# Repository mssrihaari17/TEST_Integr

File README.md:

View this project on [CADLAB.io](https://cadlab.io/project/29905). 

# TEST_Integr

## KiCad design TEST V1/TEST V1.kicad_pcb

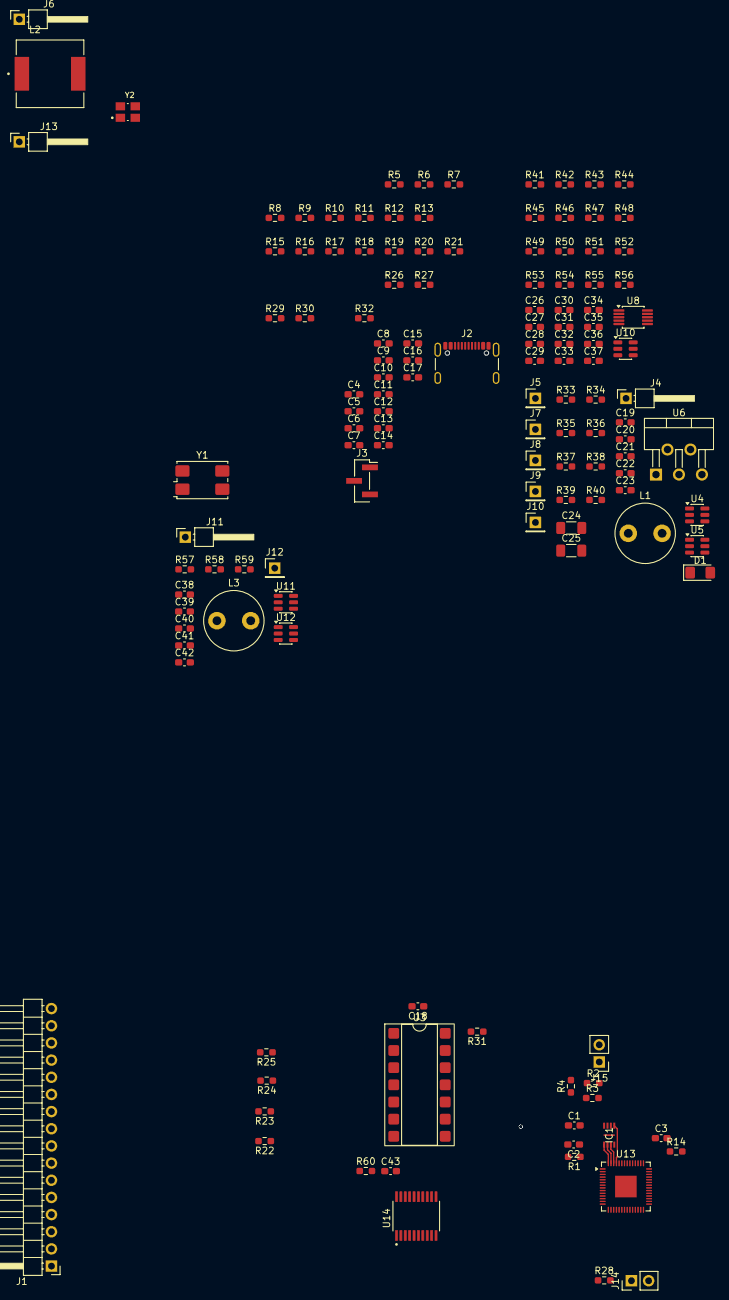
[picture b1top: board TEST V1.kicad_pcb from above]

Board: 2 copper layers, 135 parts (0 on the bottom side), 107 nets.

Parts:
C1, C3, C6, C15: 2u2; C_0603_1608Metric_Pad1.08x0.95mm_HandSolder
C2, C4, C5, C7, C8, C9, C10, C11, C12, C13, C14, C18, C20, C31, C32, C33, C37, C39, C43: 100n; C_0603_1608Metric_Pad1.08x0.95mm_HandSolder
C16, C17: 27p; C_0603_1608Metric_Pad1.08x0.95mm_HandSolder
C19, C26, C27, C30, C34, C35, C36, C38: 10u; C_0603_1608Metric_Pad1.08x0.95mm_HandSolder
C21, C40: 0.1u; C_0603_1608Metric_Pad1.08x0.95mm_HandSolder
C22, C23, C41, C42: 22u; C_0603_1608Metric_Pad1.08x0.95mm_HandSolder
C24, C25: C_Polarized; C_1206_3216Metric_Pad1.33x1.80mm_HandSolder
C28: 10n; C_0603_1608Metric_Pad1.08x0.95mm_HandSolder
C29: 1u; C_0603_1608Metric_Pad1.08x0.95mm_HandSolder
D1: 1N5820; D_1206_3216Metric_Pad1.42x1.75mm_HandSolder
IC1: W25Q16JVUXIQ; SON50P300X200X60-9N
J1: Conn_01x16_Socket; PinHeader_1x16_P2.54mm_Horizontal
J2: USB_C_Receptacle_USB2.0_14P; USB_C_Receptacle_GCT_USB4105-xx-A_16P_TopMnt_Horizontal
J3: Conn_01x03_Socket; PinHeader_1x03_P2.00mm_Vertical_SMD_Pin1Right
J4, J6, J11, J13: Conn_01x02_Pin; PinHeader_1x01_P2.54mm_Horizontal
J5, J12: PinHeader_1x01_P2.54mm_Vertical
J7, J8, J9, J10: Conn_01x01_Pin; PinHeader_1x01_P2.54mm_Vertical
J14, J15: Conn_01x02_Pin; PinHeader_1x02_P2.54mm_Vertical
L1, L3: 16u; L_Radial_D8.7mm_P5.00mm_Fastron_07HCP
L2: 33u; IND_1274AS-H-150M=P3
R1, R3, R14, R18, R19, R20, R31, R60: 0; R_0603_1608Metric_Pad0.98x0.95mm_HandSolder
R2, R32, R48, R49: 1k; R_0603_1608Metric_Pad0.98x0.95mm_HandSolder
R4, R28, R35, R50, R51, R53, R55, R59: 10k; R_0603_1608Metric_Pad0.98x0.95mm_HandSolder
R5, R6: 27R; R_0603_1608Metric_Pad0.98x0.95mm_HandSolder
R7, R8, R9, R10, R11, R12, R13, R15, R36, R37, R38, R39, R40, R41, R44, R45, R46, R47, R52, R54, R56: 0R; R_0603_1608Metric_Pad0.98x0.95mm_HandSolder
R16, R17: 1k5; R_0603_1608Metric_Pad0.98x0.95mm_HandSolder
R21: 200R; R_0603_1608Metric_Pad0.98x0.95mm_HandSolder
R22, R23, R24, R25: 100R; R_0603_1608Metric_Pad0.98x0.95mm_HandSolder
R26, R27: 5K1; R_0603_1608Metric_Pad0.98x0.95mm_HandSolder
R29: 5K6; R_0603_1608Metric_Pad0.98x0.95mm_HandSolder
R30: 10K; R_0603_1608Metric_Pad0.98x0.95mm_HandSolder
R33, R57: 100k; R_0603_1608Metric_Pad0.98x0.95mm_HandSolder
R34, R58: 190k; R_0603_1608Metric_Pad0.98x0.95mm_HandSolder
R42, R43: 2.4k; R_0603_1608Metric_Pad0.98x0.95mm_HandSolder
U3: 74AHCT125; DIP-14_W7.62mm_SMDSocket_SmallPads
U4, U11: TPS54202DDC; SOT-23-6
U5, U10, U12: MCP4725A2T-ECH; SOT-23-6
U6: LM2596T-5; TO-220-5_P3.4x3.7mm_StaggerOdd_Lead3.8mm_Vertical
U8: AD9833; MSOP-10_3x3mm_P0.5mm
U13: RP2040; QFN-56-1EP_7x7mm_P0.4mm_EP3.2x3.2mm
U14: SN74LVC244APWT; SOP65P640X120-20N
Y1: Crystal_12MHz; Crystal_SMD_7050-4Pin_7.0x5.0mm
Y2: 25 MHz; XTAL_C3E-16.000-12-1015-X-M

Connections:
3v3: J1.15, R1.1, R3.1, R15.2, R16.1, R17.1, R18.1, R19.1, R20.1, R28.1, R45.2, R46.2, R60.1, U5.3 (VDD), U5.6 (A0), U12.3 (VDD), U12.6 (A0)
5V: R31.1, R47.2, R56.2
12V: R44.1, R54.1
+1V1: C3.1, R14.1, U13.45 (VREG_VOUT)
-12V: R41.1, R52.1
/DVDD: C4.1, C5.1, R14.2, U13.23 (DVDD), U13.50 (DVDD)
/Fn Gen/FG_OUT: R42.1, U8.10 (VOUT)
/Fn Gen/OFFSET: R50.1, U10.1 (VOUT)
/GPIO8: U3.2, U13.11 (GPIO8)
/GPIO9: U3.5, U13.12 (GPIO9)
/GPIO10: U3.9, U13.13 (GPIO10)
/GPIO11: U3.12, U13.14 (GPIO11)
/GPIO24: R29.2, R30.1, U13.36 (GPIO24)
/IOVDD: R7.1, R8.1, R9.1, R10.1, R11.1, R12.1, R13.1
/LA0_IN: J1.1, U14.2 (1A1)
/LA1_IN: J1.2, U14.4 (1A2)
/LA2_IN: J1.3, U14.6 (1A3)
/LA3_IN: J1.4, U14.8 (1A4)
/LA4_IN: J1.5, U14.11 (2A1)
/LA5_IN: J1.6, U14.13 (2A2)
/LA6_IN: J1.7, U14.15 (2A3)
/LA7_IN: J1.8, U14.17 (2A4)
/PG0_OUT: J1.9, R22.2
/PG1_OUT: J1.10, R23.2
/PG2_OUT: J1.11, R24.2
/PG3_OUT: J1.12, R25.2
/POWER SUPPLY/EN: J5.1, R33.1, U4.5 (EN)
/POWER SUPPLY/RPS_VOUT: C22.1, C23.1, J6.1, L1.2, R34.1
/POWER SUPPLY/TPS_FB: R34.2, R35.1, U4.4 (FB), U5.1 (VOUT)
/POWER SUPPLY/VIN: C24.1, R36.2, R37.1
/POWER SUPPLY/VOUT: C25.1, L2.2, R39.2, R40.1
/QSPI_CSN: IC1.1 (~CS), R2.1, R4.2, U13.56 (QSPI_SS)
/QSPI_SCLK: IC1.6 (CLK), U13.52 (QSPI_SCLK)
/QSPI_SD0: IC1.5 (DI_(IO0)), U13.53 (QSPI_SD0)
/QSPI_SD1: IC1.2 (DO_(IO1)), U13.55 (QSPI_SD1)
/QSPI_SD2: IC1.3 (~WP_(IO2)), U13.54 (QSPI_SD2)
/QSPI_SD3: IC1.7 (~HOLD_OR_RESET_(IO3)), U13.51 (QSPI_SD3)
/RPS/EN: J12.1, R57.1, U11.5 (EN)
/RPS/RPS_VOUT: C41.1, C42.1, J13.1, L3.2, R58.1
/RPS/TPS_FB: R58.2, R59.1, U11.4 (FB), U12.1 (VOUT)
/RUN: J14.1, R28.2, U13.26 (RUN)
/SWCLK: J3.1, U13.24 (SWCLK)
/SWD: J3.2, U13.25 (SWD)
/USB_DM: J2.A7 (D-), J2.B7 (D-), R6.2
/USB_DP: J2.A6 (D+), J2.B6 (D+), R5.2
/VBUS: J2.A4 (VBUS), J2.A9 (VBUS), J2.B4 (VBUS), J2.B9 (VBUS), R29.1
/XIN: C16.1, U13.20 (XIN), Y1.1
/XOUT: R32.1, U13.21 (XOUT)
ADC_AVDD: C14.1, C15.1, R21.1, U13.43 (ADC_AVDD)
GND: C1.1, C2.2, C3.2, C4.2, C5.2, C6.2, C7.2, C8.2, C9.2, C10.2, C11.2, C12.2, C13.2, C14.2, C15.2, C16.2, C17.2, C18.2, C19.2, C20.2, C22.2, C23.2, C24.2, C25.2, C26.1, C27.2, C29.1, C30.1, C31.1, C32.1, C33.2, C34.1, C35.2, C36.1, C37.1, C38.2, C39.2, C41.2, C42.2, C43.2, D1.2 (A), IC1.4 (GND), J1.16, J2.A1 (GND), J2.A12 (GND), J2.B1 (GND), J2.B12 (GND), J2.S1 (SHIELD), J3.3, J8.1, J10.1, J14.2, J15.2, R26.2, R27.2, R30.2, R33.2, R35.2, R43.1, R49.2, R57.2, R59.2, U3.1, U3.4, U3.7 (GND), U3.10, U3.13, U4.1 (GND), U5.2 (VSS), U6.3 (GND), U6.5 (~ON/OFF), U8.4 (DGND), U8.9 (AGND), U10.2 (VSS), U10.6 (A0), U11.1 (GND), U12.2 (VSS), U13.19 (TESTEN), U13.57 (GND), U14.1 (~1OE), U14.10 (GND), U14.19 (~2OE), Y1.2, Y1.4, Y2.2 (GND), Y2.4 (GND)
I2C_SCL: R17.2, U10.5 (SCL), U12.5 (SCL), U13.16 (GPIO13)
I2C_SDA: R16.2, U10.4 (SDA), U12.4 (SDA), U13.15 (GPIO12)
unnamed: C17.1, R32.2, Y1.3
unnamed: C30.2, C32.2, R47.1, R48.1
unnamed: C31.2, R46.1, Y2.1
unnamed: D1.1 (K), L2.1, R38.2
unnamed: C1.2, C2.1, IC1.8 (VCC), R1.2
unnamed: J2.A5 (CC1), R26.1
unnamed: J2.B5 (CC2), R27.1
unnamed: C19.1, C20.1, J4.1, U4.3 (VIN)
unnamed: J7.1, R36.1
unnamed: J9.1, R40.2
unnamed: C38.1, C39.1, J11.1, U11.3 (VIN)
unnamed: J15.1, R2.2
unnamed: R3.2, R4.1
unnamed: R20.2, R21.2
unnamed: R22.1, U3.3
unnamed: R23.1, U3.6
unnamed: R24.1, U3.8
unnamed: R25.1, U3.11
unnamed: R48.2, R49.1, R53.1
unnamed: C9.1, R19.2
unnamed: C18.1, R31.2, U3.14 (VCC)
unnamed: C21.1, U4.6 (BOOT)
unnamed: C21.2, L1.1, U4.2 (SW)
unnamed: R39.1, U6.4 (FB)
unnamed: R38.1, U6.2 (OUT)
unnamed: R37.2, U6.1 (VIN)
unnamed: C27.1, R44.2
unnamed: C26.2, R41.2
unnamed: C33.1, U8.3 (CAP/2.5V)
unnamed: C28.2, U8.1 (COMP)
unnamed: U8.5 (MCLK), Y2.3
unnamed: C28.1, C29.2, R45.1, U8.2 (VDD)
unnamed: R50.2, R51.2
unnamed: R53.2, R55.1
unnamed: C35.1, R54.2
unnamed: C34.2, R52.2
unnamed: C36.2, C37.2, R56.1, U10.3 (VDD)
unnamed: C40.1, U11.6 (BOOT)
unnamed: C40.2, L3.1, U11.2 (SW)
unnamed: U13.2 (GPIO0), U14.18 (1Y1)
unnamed: U13.3 (GPIO1), U14.16 (1Y2)
unnamed: U13.4 (GPIO2), U14.14 (1Y3)
unnamed: U13.5 (GPIO3), U14.12 (1Y4)
unnamed: U13.6 (GPIO4), U14.9 (2Y1)
unnamed: U13.7 (GPIO5), U14.7 (2Y2)
unnamed: U13.8 (GPIO6), U14.5 (2Y3)
unnamed: U13.9 (GPIO7), U14.3 (2Y4)
unnamed: R6.1, U13.46 (USB_DM)
unnamed: R5.1, U13.47 (USB_DP)
unnamed: C7.1, C8.1, C10.1, C11.1, C12.1, C13.1, R18.2, U13.1 (IOVDD), U13.10 (IOVDD), U13.22 (IOVDD), U13.33 (IOVDD), U13.42 (IOVDD), U13.48 (USB_VDD), U13.49 (IOVDD)
unnamed: C6.1, R15.1, U13.44 (VREG_IN)
unnamed: C43.1, R60.2, U14.20 (VCC)
SPI_EN: U8.8 (~FSYNC), U13.28 (GPIO17)
SPI_MOSI: U8.6 (SDATA), U13.30 (GPIO19)
SPI_SCLK: U8.7 (SCLK), U13.29 (GPIO18)

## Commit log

2026-02-05 Initial Commit
    Initial Schematic ( FEB 5 ) with few footprints attached
2026-02-05 i2c schematic correction done
2026-02-05 Updated ignore files
2026-02-05 Ignore backups and remove tracked zip files
2026-02-05 Clean KiCad repo: ignore backups, cache, and session files
2026-02-05 Updated PCB layout (routing + placement)
2026-02-05 added hierarchical sheets
2026-02-05 Integrated FG, RPS, and PCB updates
2026-02-06 updated RPS schematic
2026-02-07 all updated
2026-02-09 Backlink to CADLAB.io has been added.
2026-02-09 updated schematic of FG
2026-02-10 updated RPS sch
2026-02-10 minor changes
